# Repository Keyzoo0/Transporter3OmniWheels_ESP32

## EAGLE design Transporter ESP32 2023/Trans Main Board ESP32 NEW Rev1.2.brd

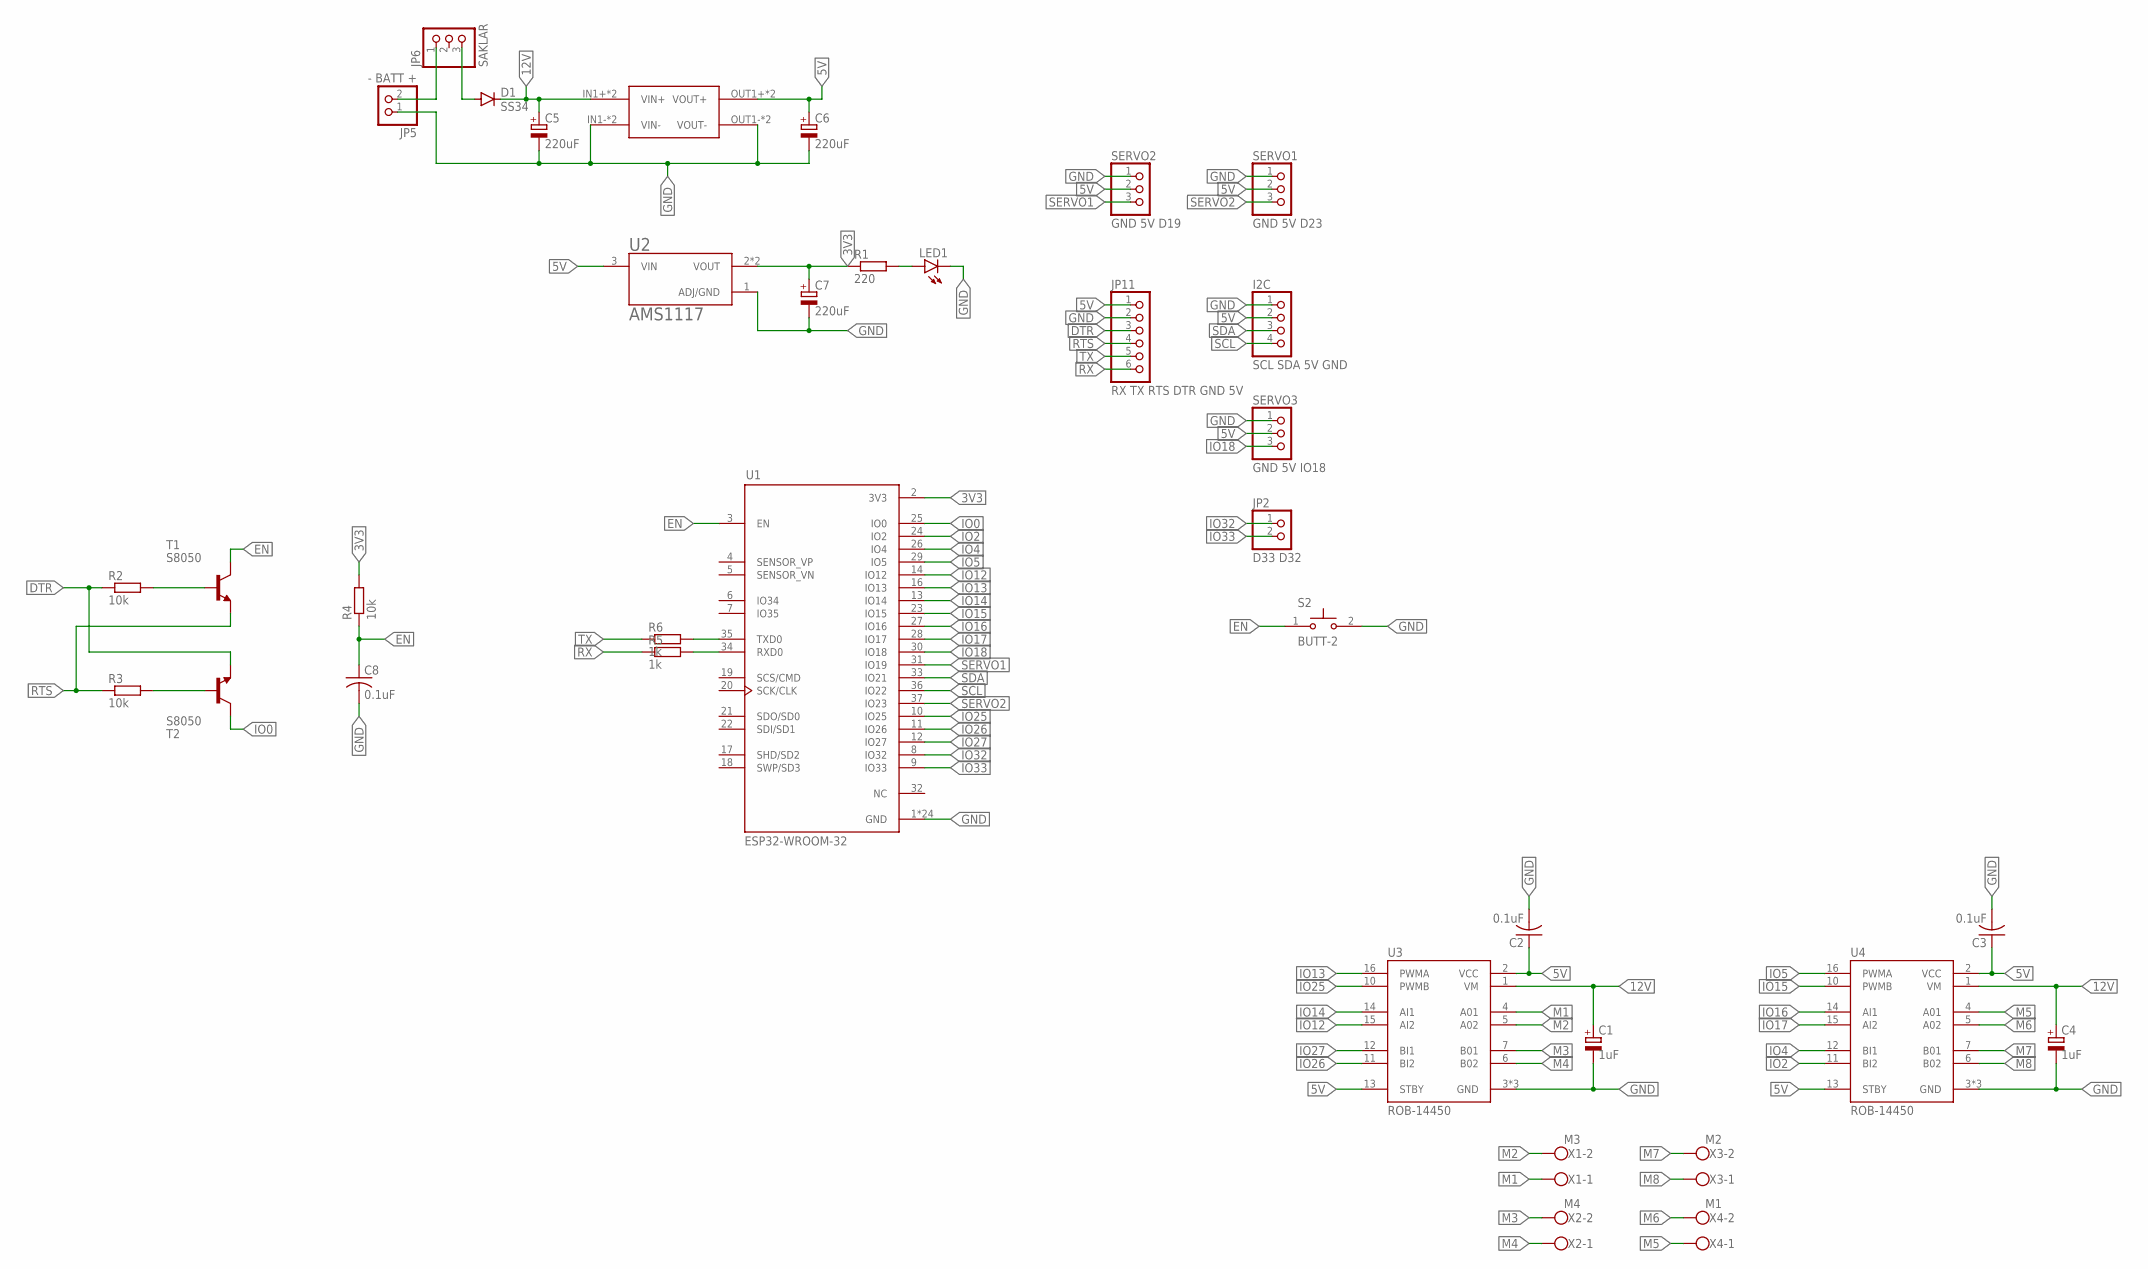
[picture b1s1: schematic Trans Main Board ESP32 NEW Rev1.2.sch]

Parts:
C1, C4: 1uF; E2-5
C2, C3, C8: 0.1uF; C1206
C5, C6, C7: 220uF; E2-5
D1: SS34; DO-214AC
I2C: SCL SDA 5V GND; 1X04
JP2: D33 D32; 1X02
JP5: - BATT +; 1X02
JP6: SAKLAR; 1X03
JP11: RX TX RTS DTR GND 5V; 1X06
LED1: LEDCHIPLED_1206; CHIPLED_1206
R1: 220; R1206
R2, R3, R4: 10k; R1206
R5, R6: 1k; R1206
S2: BUTT-2; SW_BUTT-2
SERVO1: GND 5V D23; 1X03
SERVO2: GND 5V D19; 1X03
SERVO3: GND 5V IO18; 1X03
T1, T2: S8050; SOT23
U1: ESP32-WROOM-32; MODULE_ESP32-WROOM-32
U2: AMS1117; SOT229P700X180-4N
U3, U4: ROB-14450; MODULE_ROB-14450
U$1: MP1584; DC-BRICK
X1: M3; W237-102
X2: M4; W237-102
X3: M2; W237-102
X4: M1; W237-102

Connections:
3V3: C7.+, R1.1, R4.2, U1.2 (3V3), U2.2 (VOUT), U2.4 (VOUT)
5V: C2.1, C3.1, C6.+, I2C.2, JP11.1, SERVO1.2, SERVO2.2, SERVO3.2, U2.3 (VIN), U3.2 (VCC), U3.13 (STBY), U4.2 (VCC), U4.13 (STBY), U$1.OUT1+ (VOUT+), U$1.OUT2+ (VOUT+)
12V: C1.+, C4.+, C5.+, D1.C, U3.1 (VM), U4.1 (VM), U$1.IN1+ (VIN+), U$1.IN2+ (VIN+)
DTR: JP11.3, R2.1, T2.2 (E)
EN: C8.1, R4.1, S2.1, T1.3 (C), U1.3 (EN)
GND: C1.-, C2.2, C3.2, C4.-, C5.-, C6.-, C7.-, C8.2, I2C.1, JP5.1, JP11.2, LED1.C, S2.2, SERVO1.1, SERVO2.1, SERVO3.1, U1.1 (GND), U1.15 (GND), U1.38 (GND), U1.39_1 (GND), U1.39_2 (GND), U1.39_3 (GND), U1.39_4 (GND), U1.39_5 (GND), U1.39_6 (GND), U1.39_7 (GND), U1.39_8 (GND), U1.39_9 (GND), U1.39_10 (GND), U1.39_11 (GND), U1.39_12 (GND), U1.39_13 (GND), U1.39_14 (GND), U1.39_15 (GND), U1.39_16 (GND), U1.39_17 (GND), U1.39_18 (GND), U1.39_19 (GND), U1.39_20 (GND), U1.39_21 (GND), U2.1 (ADJ/GND), U3.3 (GND), U3.8 (GND), U3.9 (GND), U4.3 (GND), U4.8 (GND), U4.9 (GND), U$1.IN1- (VIN-), U$1.IN2- (VIN-), U$1.OUT1- (VOUT-), U$1.OUT2- (VOUT-)
IO0: T2.3 (C), U1.25 (IO0)
IO2: U1.24 (IO2), U4.11 (BI2)
IO4: U1.26 (IO4), U4.12 (BI1)
IO5: U1.29 (IO5), U4.16 (PWMA)
IO12: U1.14 (IO12), U3.15 (AI2)
IO13: U1.16 (IO13), U3.16 (PWMA)
IO14: U1.13 (IO14), U3.14 (AI1)
IO15: U1.23 (IO15), U4.10 (PWMB)
IO16: U1.27 (IO16), U4.14 (AI1)
IO17: U1.28 (IO17), U4.15 (AI2)
IO18: SERVO3.3, U1.30 (IO18)
IO25: U1.10 (IO25), U3.10 (PWMB)
IO26: U1.11 (IO26), U3.11 (BI2)
IO27: U1.12 (IO27), U3.12 (BI1)
IO32: JP2.1, U1.8 (IO32)
IO33: JP2.2, U1.9 (IO33)
M1: U3.4 (A01), X1.1
M2: U3.5 (A02), X1.2
M3: U3.7 (B01), X2.2
M4: U3.6 (B02), X2.1
M5: U4.4 (A01), X4.1
M6: U4.5 (A02), X4.2
M7: U4.7 (B01), X3.2
M8: U4.6 (B02), X3.1
unnamed: JP5.2, JP6.1
unnamed: D1.A, JP6.3
unnamed: R2.2, T1.1 (B)
unnamed: R3.2, T2.1 (B)
unnamed: LED1.A, R1.2
unnamed: R6.2, U1.35 (TXD0)
unnamed: R5.2, U1.34 (RXD0)
RTS: JP11.4, R3.1, T1.2 (E)
RX: JP11.6, R5.1
SCL: I2C.4, U1.36 (IO22)
SDA: I2C.3, U1.33 (IO21)
SERVO1: SERVO2.3, U1.31 (IO19)
SERVO2: SERVO1.3, U1.37 (IO23)
TX: JP11.5, R6.1

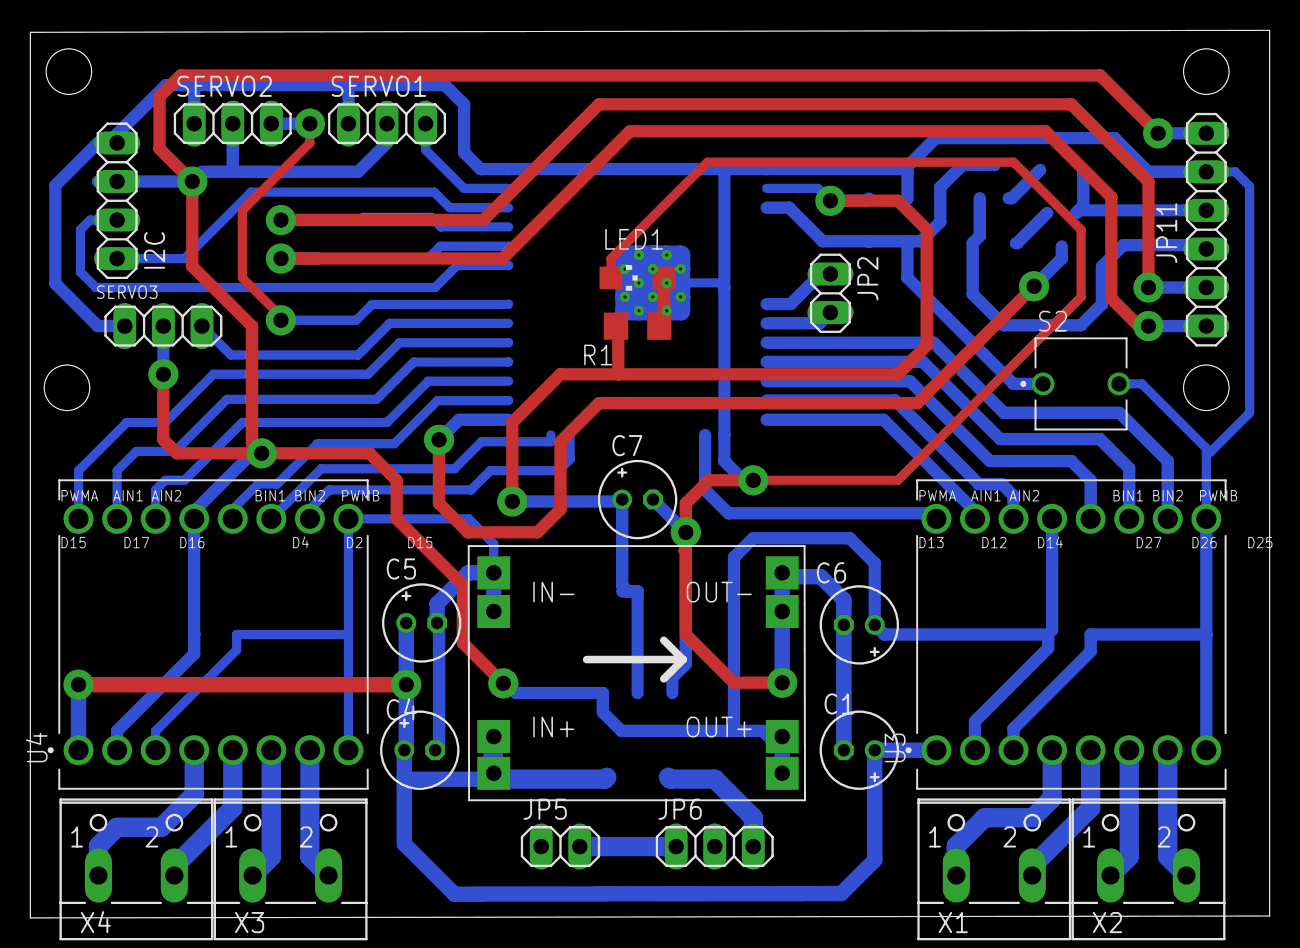
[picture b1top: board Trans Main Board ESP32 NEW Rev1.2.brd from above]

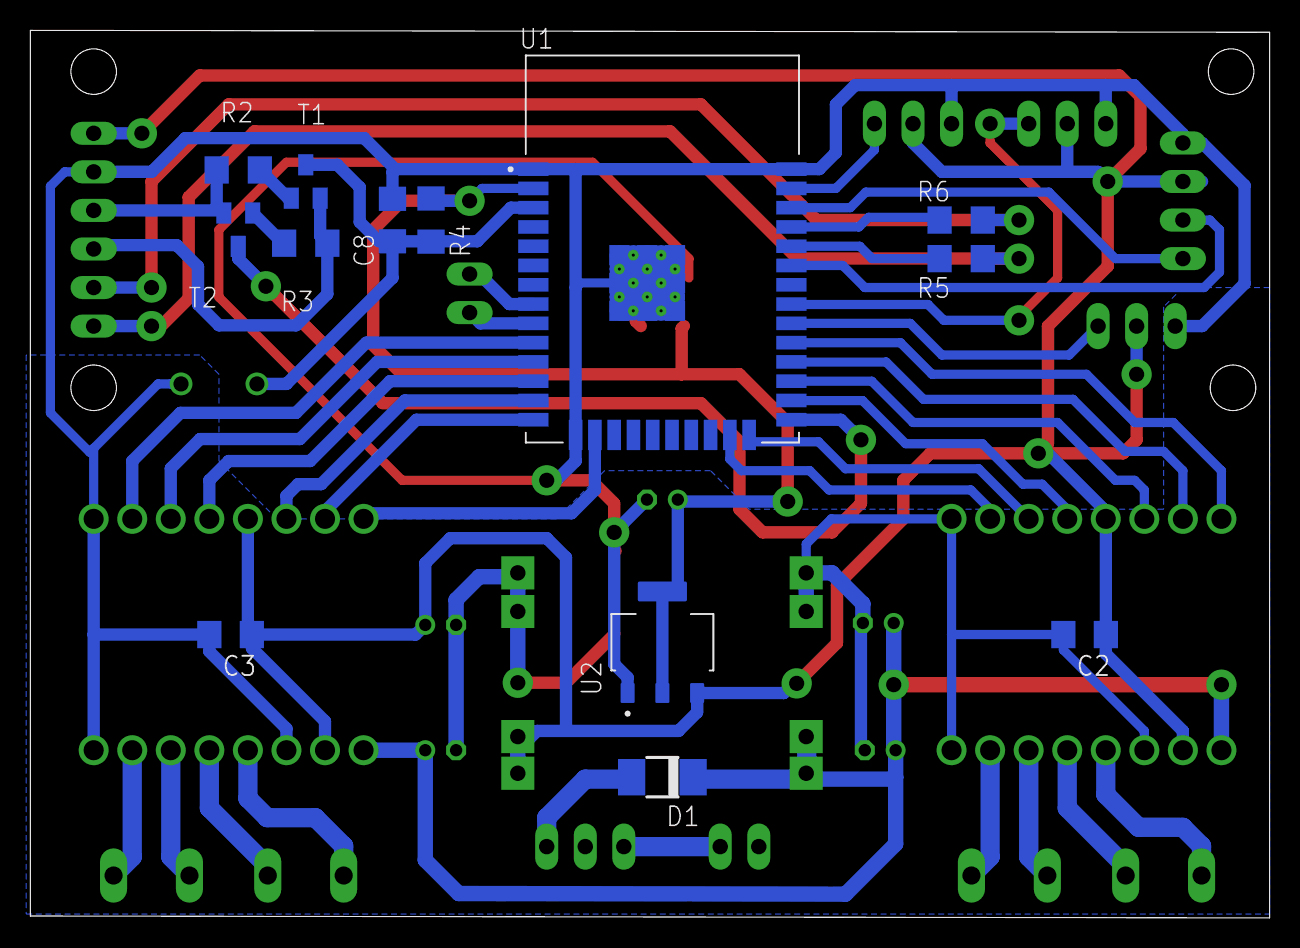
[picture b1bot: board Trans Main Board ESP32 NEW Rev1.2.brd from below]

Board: 2 copper layers, 81.6 x 58.5 mm, 36 parts (13 on the bottom side), 44 nets.
